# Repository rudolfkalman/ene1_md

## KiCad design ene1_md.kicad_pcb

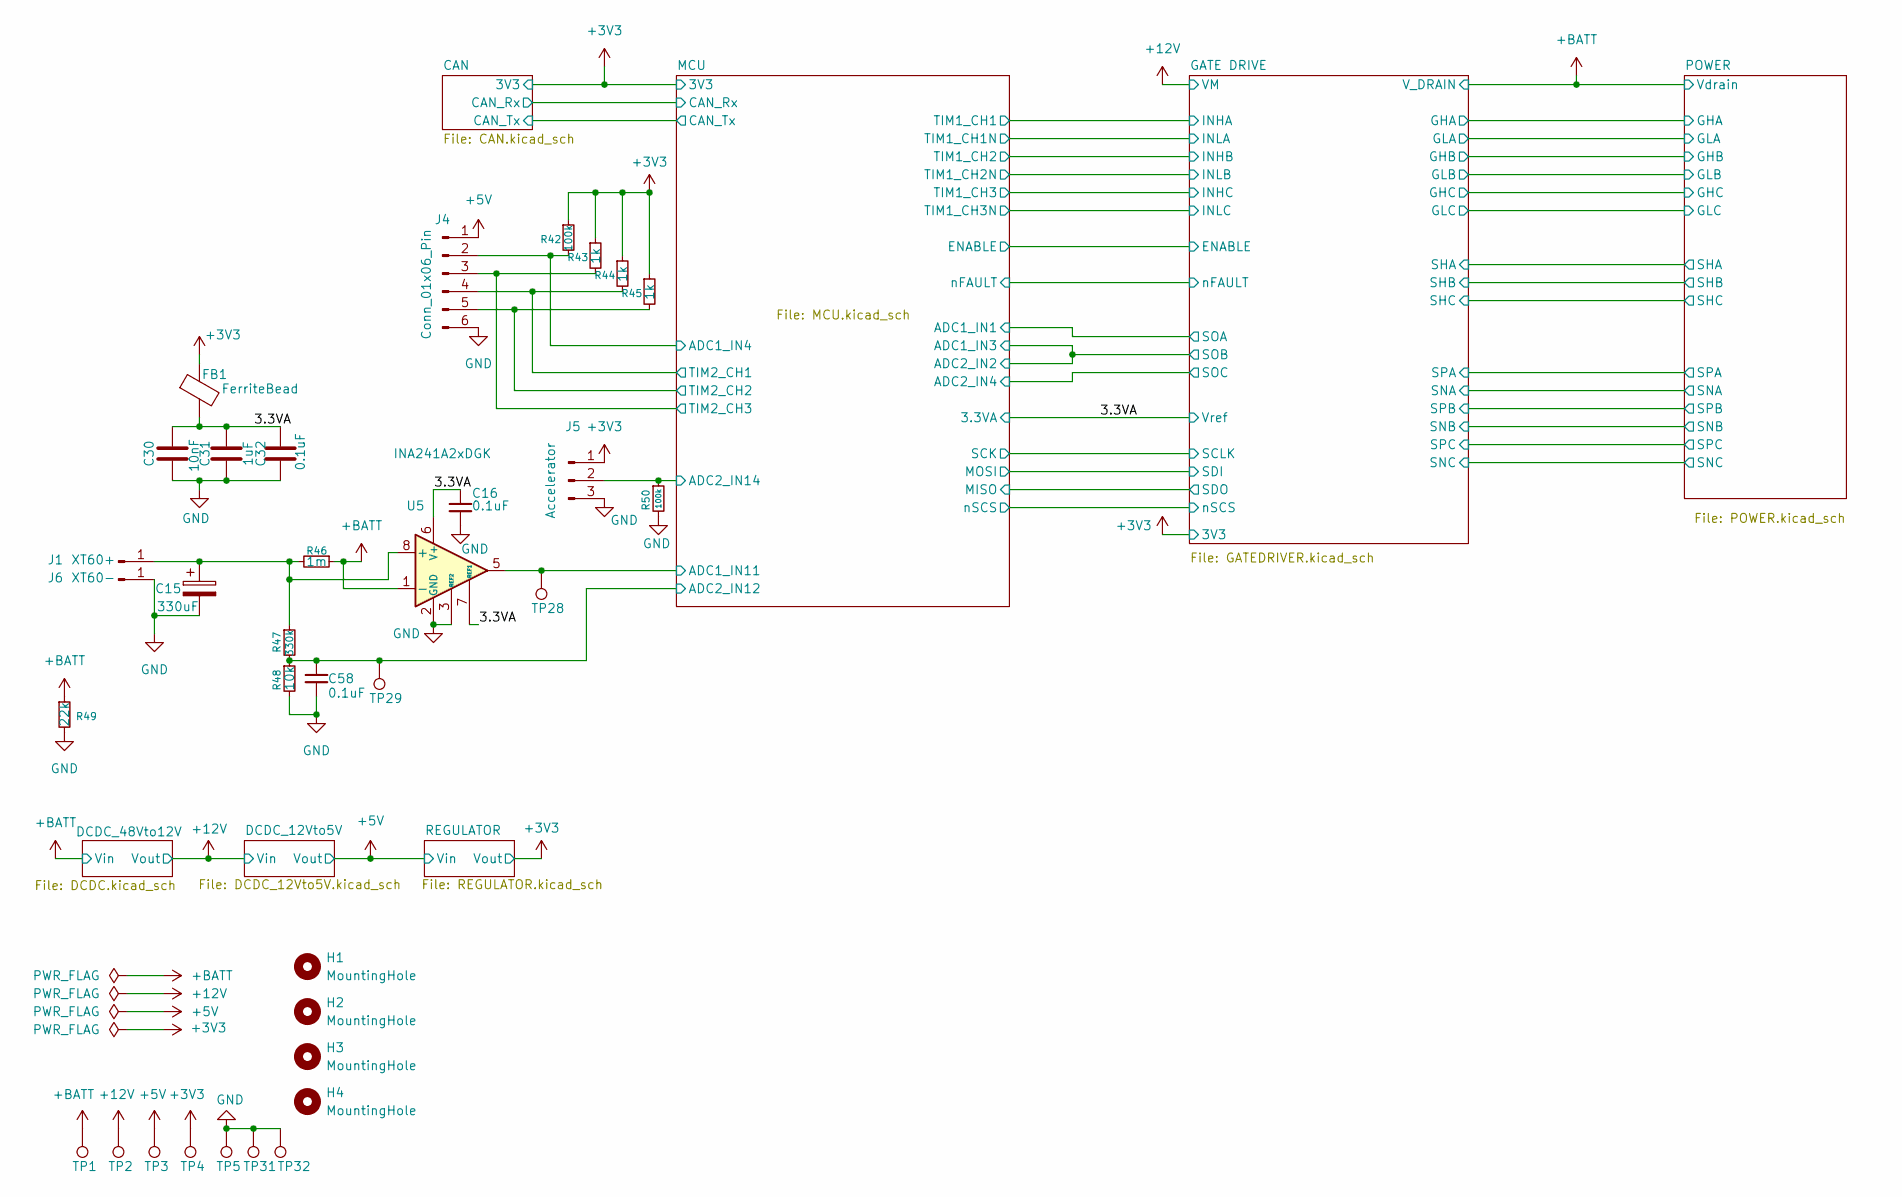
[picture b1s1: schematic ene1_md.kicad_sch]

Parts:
C15: 330uF; CP_Radial_D12.5mm_P5.00mm
C16, C32, C58: 0.1uF; C_0603_1608Metric
C30: 10nF; C_0603_1608Metric
C31: 1uF; C_0603_1608Metric
FB1: FerriteBead; L_0603_1608Metric
H1, H2, H3, H4: MountingHole; MountingHole_3.2mm_M3
J1: XT60+; SolderWirePad_1x01_SMD_5x10mm
J4: Conn_01x06_Pin; JST_XH_B6B-XH-A_1x06_P2.50mm_Vertical
J5: Accelerator; JST_XH_B6B-XH-A_1x06_P2.50mm_Vertical
J6: XT60-; SolderWirePad_1x01_SMD_5x10mm
R42: 100k; R_0805_2012Metric
R43, R44, R45: 1k; R_0603_1608Metric
R46: 1m; R_Stackpole_CSNL2512FT1L00
R47: 330k; R_0805_2012Metric
R48: 10k; R_0603_1608Metric
R49: 22k; R_Axial_DIN0207_L6.3mm_D2.5mm_P10.16mm_Horizontal
R50: 100k; R_0603_1608Metric
TP1, TP2, TP3, TP4, TP5, TP28, TP29, TP31, TP32: TestPoint; TestPoint_Pad_D1.5mm
U5: INA241A2xDGK; VSSOP-8_3x3mm_P0.65mm

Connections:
+3V3: FB1.1, J5.1, R42.1, R43.1, R44.1, R45.1, TP4.1 (1_1); also elsewhere on the board
+5V: J4.1, TP3.1 (1_1); also elsewhere on the board
+12V: TP2.1 (1_1); also elsewhere on the board
+BATT: R46.1, R49.1, TP1.1 (1_1), U5.1 (-); also elsewhere on the board
/3.3VA: C16.1, C30.2, C31.2, C32.2, FB1.2, U5.6 (V+), U5.7 (REF1); also elsewhere on the board
/MCU/ADC1_IN4: J4.2, R42.2; also elsewhere on the board
/MCU/ADC1_IN11: TP28.1 (1_1), U5.5; also elsewhere on the board
/MCU/ADC2_IN12: C58.1, R47.2, R48.1, TP29.1 (1_1); also elsewhere on the board
/MCU/ADC2_IN14: J5.2, R50.1; also elsewhere on the board
/MCU/TIM2_CH1: J4.4, R44.2; also elsewhere on the board
/MCU/TIM2_CH2: J4.5, R45.2; also elsewhere on the board
/MCU/TIM2_CH3: J4.3, R43.2; also elsewhere on the board
GND: C15.2, C16.2, C30.1, C31.1, C32.1, C58.2, J4.6, J5.3, J6.1 (Pin_1_1), R48.2, R49.2, R50.2, TP5.1 (1_1), TP31.1 (1_1), TP32.1 (1_1), U5.2 (GND), U5.3 (REF2), U5.4 (GND); also elsewhere on the board
unnamed: C15.1, J1.1 (Pin_1_1), R46.2, R47.1, U5.8 (+)

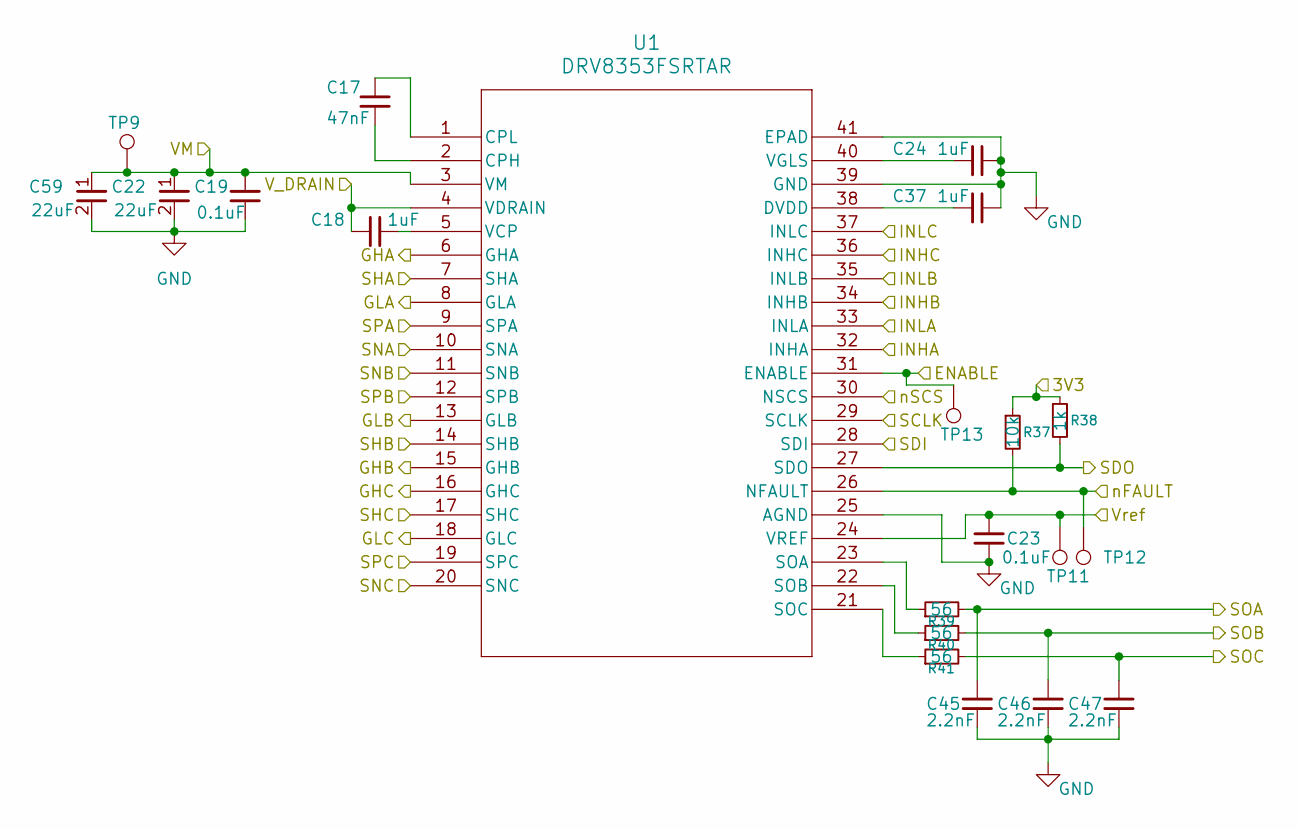
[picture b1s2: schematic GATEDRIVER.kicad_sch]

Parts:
C17: 47nF; C_0805_2012Metric
C18, C24, C37: 1uF; C_0805_2012Metric
C19, C23: 0.1uF; C_0603_1608Metric
C22, C59: 22uF; C_1206_3216Metric
C45, C46, C47: 2.2nF; C_0603_1608Metric
R37: 10k; R_0603_1608Metric
R38: 1k; R_0603_1608Metric
R39, R40, R41: 56; R_0603_1608Metric
TP9, TP11, TP12, TP13: TestPoint; TestPoint_Pad_D1.5mm
U1: DRV8353FSRTAR; WQFN40_RTA_TEX

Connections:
+3V3: R37.1, R38.1; also elsewhere on the board
+12V: C19.1, C22.1, C59.1, TP9.1 (1_1), U1.3 (VM); also elsewhere on the board
+BATT: C18.1, U1.4 (VDRAIN); also elsewhere on the board
/3.3VA: C23.1, TP11.1 (1_1), U1.24 (VREF); also elsewhere on the board
/GATE DRIVE/ENABLE: TP13.1 (1_1), U1.31 (ENABLE); also elsewhere on the board
/GATE DRIVE/GHA: U1.6 (GHA); also elsewhere on the board
/GATE DRIVE/GHB: U1.15 (GHB); also elsewhere on the board
/GATE DRIVE/GHC: U1.16 (GHC); also elsewhere on the board
/GATE DRIVE/GLA: U1.8 (GLA); also elsewhere on the board
/GATE DRIVE/GLB: U1.13 (GLB); also elsewhere on the board
/GATE DRIVE/GLC: U1.18 (GLC); also elsewhere on the board
/GATE DRIVE/INHA: U1.32 (INHA); also elsewhere on the board
/GATE DRIVE/INHB: U1.34 (INHB); also elsewhere on the board
/GATE DRIVE/INHC: U1.36 (INHC); also elsewhere on the board
/GATE DRIVE/INLA: U1.33 (INLA); also elsewhere on the board
/GATE DRIVE/INLB: U1.35 (INLB); also elsewhere on the board
/GATE DRIVE/INLC: U1.37 (INLC); also elsewhere on the board
/GATE DRIVE/SCLK: U1.29 (SCLK); also elsewhere on the board
/GATE DRIVE/SDI: U1.28 (SDI); also elsewhere on the board
/GATE DRIVE/SDO: R38.2, U1.27 (SDO); also elsewhere on the board
/GATE DRIVE/SOA: C45.1, R39.2; also elsewhere on the board
/GATE DRIVE/SOB: C46.1, R40.2; also elsewhere on the board
/GATE DRIVE/SOC: C47.1, R41.2; also elsewhere on the board
/GATE DRIVE/SPA: U1.9 (SPA); also elsewhere on the board
/GATE DRIVE/SPB: U1.12 (SPB); also elsewhere on the board
/GATE DRIVE/SPC: U1.19 (SPC); also elsewhere on the board
/GATE DRIVE/nFAULT: R37.2, TP12.1 (1_1), U1.26 (NFAULT); also elsewhere on the board
/GATE DRIVE/nSCS: U1.30 (NSCS); also elsewhere on the board
/POWER/U: U1.7 (SHA); also elsewhere on the board
/POWER/V: U1.14 (SHB); also elsewhere on the board
/POWER/W: U1.17 (SHC); also elsewhere on the board
GND: C19.2, C22.2, C23.2, C24.2, C37.2, C45.2, C46.2, C47.2, C59.2, U1.10 (SNA), U1.11 (SNB), U1.20 (SNC), U1.25 (AGND), U1.39 (GND), U1.41 (EPAD); also elsewhere on the board
unnamed: C17.2, U1.2 (CPH)
unnamed: C17.1, U1.1 (CPL)
unnamed: C37.1, U1.38 (DVDD)
unnamed: R39.1, U1.23 (SOA)
unnamed: R40.1, U1.22 (SOB)
unnamed: R41.1, U1.21 (SOC)
unnamed: C18.2, U1.5 (VCP)
unnamed: C24.1, U1.40 (VGLS)

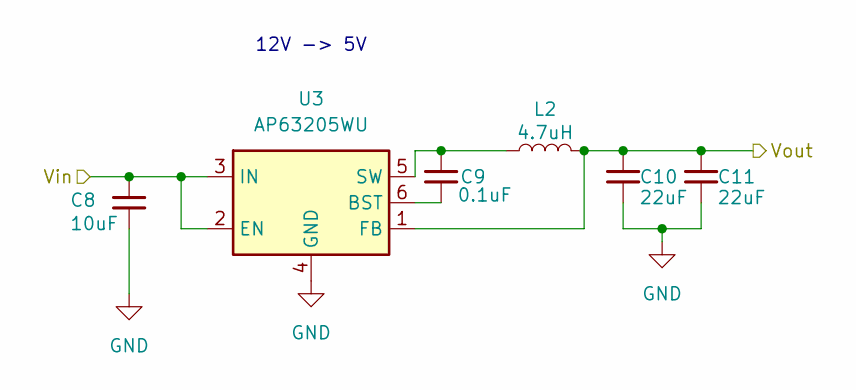
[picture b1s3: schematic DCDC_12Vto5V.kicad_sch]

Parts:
C8: 10uF; C_1206_3216Metric
C9: 0.1uF; C_0603_1608Metric
C10, C11: 22uF; C_1206_3216Metric
L2: 4.7uH; SRN5040-4R7M
U3: AP63205WU; TSOT-23-6

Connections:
+5V: C10.1, C11.1, L2.2, U3.1 (FB); also elsewhere on the board
+12V: C8.1, U3.2 (EN), U3.3 (IN); also elsewhere on the board
GND: C8.2, C10.2, C11.2, U3.4 (GND); also elsewhere on the board
unnamed: C9.2, U3.6 (BST)
unnamed: C9.1, L2.1, U3.5 (SW)

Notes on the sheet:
12V -> 5V

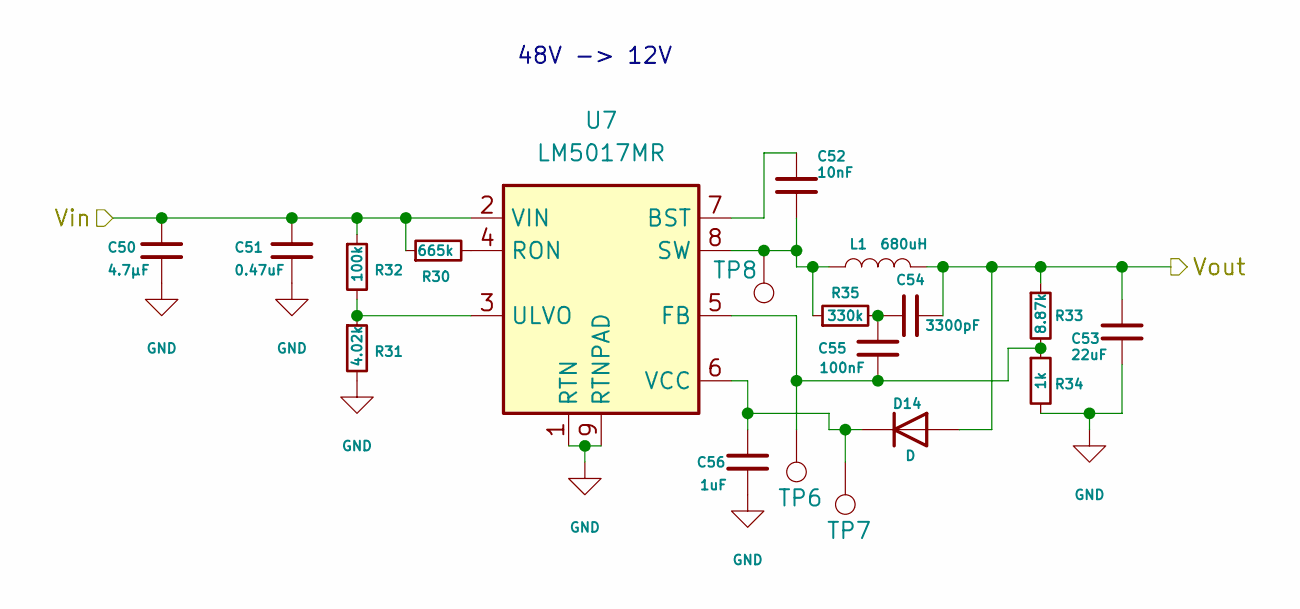
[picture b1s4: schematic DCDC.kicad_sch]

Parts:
C50: 4.7µF; C_1210_3225Metric
C51: 0.47uF; C_1206_3216Metric
C52: 10nF; C_0603_1608Metric
C53: 22uF; C_1210_3225Metric
C54: 3300pF; C_0603_1608Metric
C55: 100nF; C_0603_1608Metric
C56: 1uF; C_0603_1608Metric
D14: D; D_DO-214AC(SMA)
L1: 680uH; L_Wurth_WE-PD-1210
R30: 665k; R_0805_2012Metric
R31: 4.02k; R_0603_1608Metric
R32: 100k; R_0805_2012Metric
R33: 8.87k; R_0603_1608Metric
R34: 1k; R_0603_1608Metric
R35: 330k; R_0805_2012Metric
TP6: TestPoint; TestPoint_Pad_D1.0mm
TP7, TP8: TestPoint; TestPoint_Pad_D1.5mm
U7: LM5017MR; SOIC-8-1EP_3.9x4.9mm_P1.27mm_EP2.95x4.9mm_Mask2.71x3.4mm_Th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

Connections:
+12V: C53.1, C54.2, D14.2 (A), L1.2, R33.1; also elsewhere on the board
+BATT: C50.1, C51.1, R30.1, R32.1, U7.2 (VIN); also elsewhere on the board
GND: C50.2, C51.2, C53.2, C56.2, R31.2, R34.2, U7.1 (RTN), U7.9 (RTNPAD); also elsewhere on the board
unnamed: C54.1, C55.2, R35.2
unnamed: C56.1, D14.1 (K), TP7.1 (1_1), U7.6 (VCC)
unnamed: C52.1, U7.7 (BST)
unnamed: C55.1, R33.2, R34.1, TP6.1 (1_1), U7.5 (FB)
unnamed: R30.2, U7.4 (RON)
unnamed: C52.2, L1.1, R35.1, TP8.1 (1_1), U7.8 (SW)
unnamed: R31.1, R32.2, U7.3 (ULVO)

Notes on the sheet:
48V -> 12V

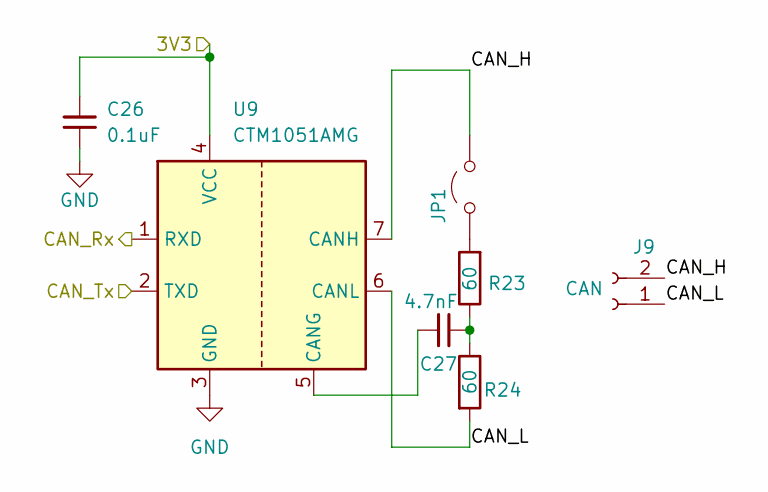
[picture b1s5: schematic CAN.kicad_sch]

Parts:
C26: 0.1uF; C_0603_1608Metric
C27: 4.7nF; C_0603_1608Metric
J9: CAN; JST_XH_B2B-XH-A_1x02_P2.50mm_Vertical
JP1: Jumper_2_Open; R_0603_1608Metric
R23, R24: 60; R_0603_1608Metric
U9: CTM1051AMG; ZLG_CTM1051AMG_12.8x10.2mm_P2.54mm

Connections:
+3V3: C26.1, U9.4 (VCC); also elsewhere on the board
/CAN/CAN_H: J9.2, JP1.2 (B), U9.7 (CANH)
/CAN/CAN_L: J9.1, R24.2, U9.6 (CANL)
/CAN/CAN_Rx: U9.1 (RXD); also elsewhere on the board
/CAN/CAN_Tx: U9.2 (TXD); also elsewhere on the board
GND: C26.2, U9.3 (GND); also elsewhere on the board
unnamed: C27.2, R23.1, R24.1
unnamed: JP1.1 (A), R23.2
unnamed: C27.1, U9.5 (CANG)

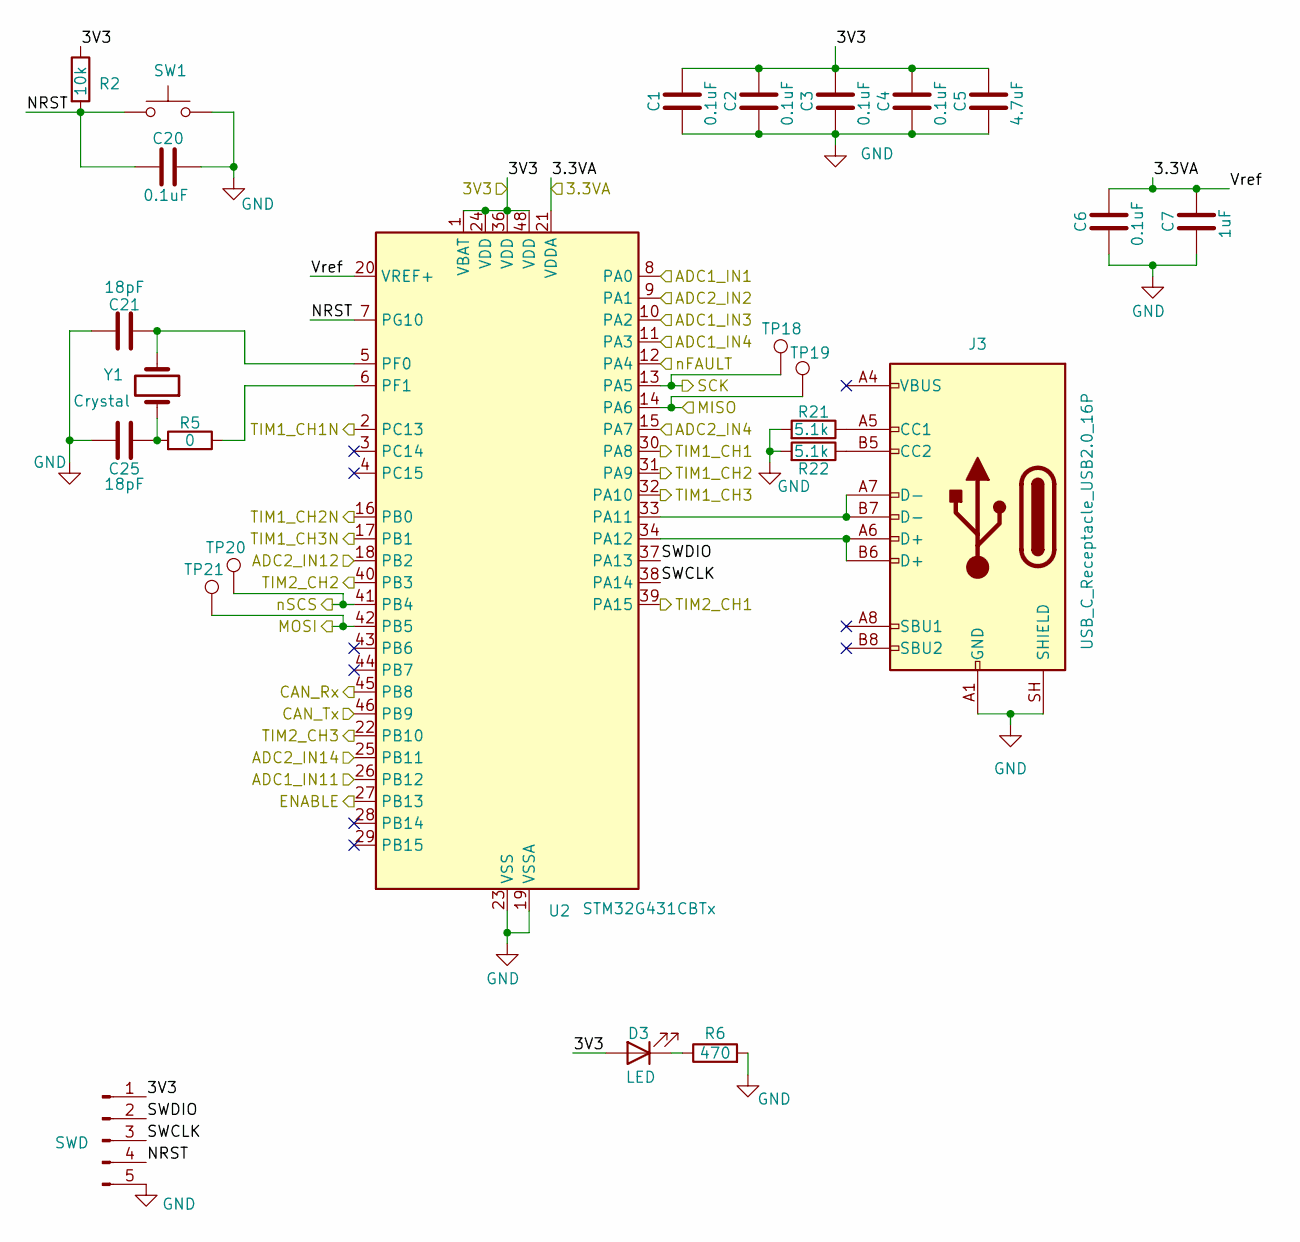
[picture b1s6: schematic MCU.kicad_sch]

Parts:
C1, C2, C3, C4, C6, C20: 0.1uF; C_0603_1608Metric
C5: 4.7uF; C_0603_1608Metric
C7: 1uF; C_0603_1608Metric
C21, C25: 18pF; C_0603_1608Metric
D3: LED; LED_0603_1608Metric
J3: USB_C_Receptacle_USB2.0_16P; USB_C_Receptacle_GCT_USB4110
R2: 10k; R_0603_1608Metric
R5: 0; R_0603_1608Metric
R6: 470; R_0603_1608Metric
R21, R22: 5.1k; R_0603_1608Metric
ST-LINK1: SWD; PinHeader_1x05_P2.54mm_Vertical
SW1: SW_Push; SW_Tactile_SPST_NO_Straight_CK_PTS636Sx25SMTRLFS
TP18, TP19, TP20, TP21: TestPoint; TestPoint_Pad_D1.5mm
U2: STM32G431CBTx; LQFP-48_7x7mm_P0.5mm
Y1: Crystal; Crystal_SMD_3225-4Pin_3.2x2.5mm

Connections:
+3V3: C1.2, C2.2, C3.2, C4.2, C5.2, D3.2 (A), R2.1, ST-LINK1.1, U2.1 (VBAT), U2.24 (VDD), U2.36 (VDD), U2.48 (VDD); also elsewhere on the board
/3.3VA: C6.2, C7.2, U2.20 (VREF+), U2.21 (VDDA); also elsewhere on the board
/CAN/CAN_Rx: U2.45 (PB8); also elsewhere on the board
/CAN/CAN_Tx: U2.46 (PB9); also elsewhere on the board
/GATE DRIVE/ENABLE: U2.27 (PB13); also elsewhere on the board
/GATE DRIVE/INHA: U2.30 (PA8); also elsewhere on the board
/GATE DRIVE/INHB: U2.31 (PA9); also elsewhere on the board
/GATE DRIVE/INHC: U2.32 (PA10); also elsewhere on the board
/GATE DRIVE/INLA: U2.2 (PC13); also elsewhere on the board
/GATE DRIVE/INLB: U2.16 (PB0); also elsewhere on the board
/GATE DRIVE/INLC: U2.17 (PB1); also elsewhere on the board
/GATE DRIVE/SCLK: TP18.1 (1_1), U2.13 (PA5); also elsewhere on the board
/GATE DRIVE/SDI: TP21.1 (1_1), U2.42 (PB5); also elsewhere on the board
/GATE DRIVE/SDO: TP19.1 (1_1), U2.14 (PA6); also elsewhere on the board
/GATE DRIVE/SOA: U2.8 (PA0); also elsewhere on the board
/GATE DRIVE/SOB: U2.9 (PA1), U2.10 (PA2); also elsewhere on the board
/GATE DRIVE/SOC: U2.15 (PA7); also elsewhere on the board
/GATE DRIVE/nFAULT: U2.12 (PA4); also elsewhere on the board
/GATE DRIVE/nSCS: TP20.1 (1_1), U2.41 (PB4); also elsewhere on the board
/MCU/ADC1_IN4: U2.11 (PA3); also elsewhere on the board
/MCU/ADC1_IN11: U2.26 (PB12); also elsewhere on the board
/MCU/ADC2_IN12: U2.18 (PB2); also elsewhere on the board
/MCU/ADC2_IN14: U2.25 (PB11); also elsewhere on the board
/MCU/NRST: C20.1, R2.2, ST-LINK1.4, SW1.1, U2.7 (PG10)
/MCU/SWCLK: ST-LINK1.3, U2.38 (PA14)
/MCU/SWDIO: ST-LINK1.2, U2.37 (PA13)
/MCU/TIM2_CH1: U2.39 (PA15); also elsewhere on the board
/MCU/TIM2_CH2: U2.40 (PB3); also elsewhere on the board
/MCU/TIM2_CH3: U2.22 (PB10); also elsewhere on the board
GND: C1.1, C2.1, C3.1, C4.1, C5.1, C6.1, C7.1, C20.2, C21.2, C25.1, J3.A1 (GND), J3.A12 (GND), J3.B1 (GND), J3.B12 (GND), J3.SH (SHIELD), R6.2, R21.2, R22.2, ST-LINK1.5, SW1.2, U2.19 (VSSA), U2.23 (VSS), U2.35 (VSS), U2.47 (VSS); also elsewhere on the board
unnamed: C25.2, R5.2, Y1.1
unnamed: D3.1 (K), R6.1
unnamed: J3.A5 (CC1), R21.1
unnamed: J3.B5 (CC2), R22.1
unnamed: J3.A7 (D-), J3.B7 (D-), U2.33 (PA11)
unnamed: J3.A6 (D+), J3.B6 (D+), U2.34 (PA12)
unnamed: C21.1, U2.5 (PF0), Y1.2
unnamed: R5.1, U2.6 (PF1)

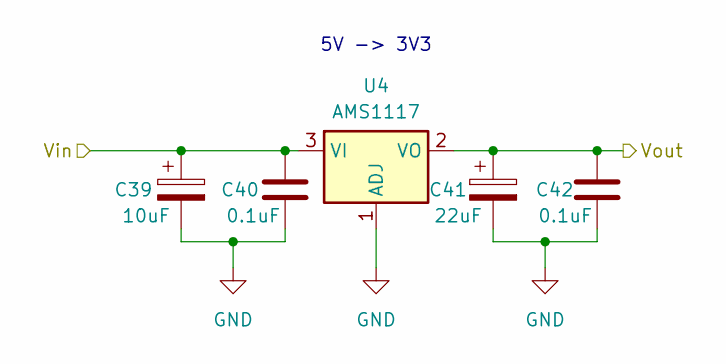
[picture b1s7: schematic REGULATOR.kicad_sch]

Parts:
C39: 10uF; C_CASE-A-3216-18(mm)
C40, C42: 0.1uF; C_0603_1608Metric
C41: 22uF; C_CASE-A-3216-18(mm)
U4: AMS1117; SOT-223-3_TabPin2

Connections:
+3V3: C41.1, C42.1, U4.2 (VO); also elsewhere on the board
+5V: C39.1, C40.1, U4.3 (VI); also elsewhere on the board
GND: C39.2, C40.2, C41.2, C42.2, U4.1 (ADJ); also elsewhere on the board

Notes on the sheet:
5V -> 3V3

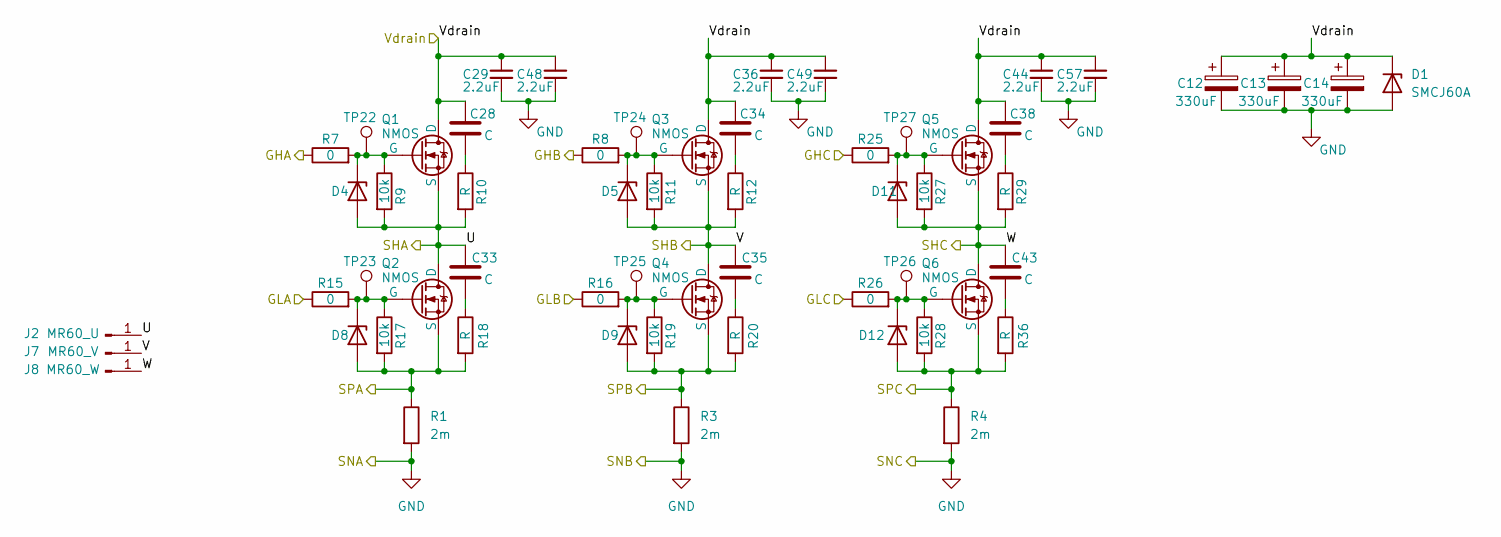
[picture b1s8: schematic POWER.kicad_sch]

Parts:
C12, C13, C14: 330uF; CP_Radial_D12.5mm_P5.00mm
C28, C33, C34, C35, C38, C43: C; C_0805_2012Metric
C29, C36, C44, C48, C49, C57: 2.2uF; C_1210_3225Metric
D1: SMCJ60A; D_SMC
D4, D5, D8, D9, D11, D12: D_Zener; D_SOD-123
J2: MR60_U; SolderWirePad_1x01_SMD_5x10mm
J7: MR60_V; SolderWirePad_1x01_SMD_5x10mm
J8: MR60_W; SolderWirePad_1x01_SMD_5x10mm
Q1, Q2, Q3, Q4, Q5, Q6: NMOS; TPH2R70AR5_SOP-Advance-N
R1, R3, R4: 2m; R_Bourns_CRE2512-FZ-R002E-3
R7, R8, R15, R16, R25, R26: 0; R_0603_1608Metric
R9, R11, R17, R19, R27, R28: 10k; R_0603_1608Metric
R10, R12, R18, R20, R29, R36: R; R_0805_2012Metric
TP22, TP23, TP24, TP25, TP26, TP27: TestPoint; TestPoint_Pad_D1.5mm

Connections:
+BATT: C12.1, C13.1, C14.1, C28.1, C29.1, C34.1, C36.1, C38.1, C44.1, C48.1, C49.1, C57.1, D1.1 (K), Q1.1 (D), Q3.1 (D), Q5.1 (D); also elsewhere on the board
/GATE DRIVE/GHA: R7.1; also elsewhere on the board
/GATE DRIVE/GHB: R8.1; also elsewhere on the board
/GATE DRIVE/GHC: R25.1; also elsewhere on the board
/GATE DRIVE/GLA: R15.1; also elsewhere on the board
/GATE DRIVE/GLB: R16.1; also elsewhere on the board
/GATE DRIVE/GLC: R26.1; also elsewhere on the board
/GATE DRIVE/SPA: D8.2 (A), Q2.3 (S), R1.1, R17.2, R18.2; also elsewhere on the board
/GATE DRIVE/SPB: D9.2 (A), Q4.3 (S), R3.1, R19.2, R20.2; also elsewhere on the board
/GATE DRIVE/SPC: D12.2 (A), Q6.3 (S), R4.1, R28.2, R36.2; also elsewhere on the board
/POWER/U: C33.1, D4.2 (A), J2.1 (Pin_1_1), Q1.3 (S), Q2.1 (D), R9.2, R10.2; also elsewhere on the board
/POWER/V: C35.1, D5.2 (A), J7.1 (Pin_1_1), Q3.3 (S), Q4.1 (D), R11.2, R12.2; also elsewhere on the board
/POWER/W: C43.1, D11.2 (A), J8.1 (Pin_1_1), Q5.3 (S), Q6.1 (D), R27.2, R29.2; also elsewhere on the board
GND: C12.2, C13.2, C14.2, C29.2, C36.2, C44.2, C48.2, C49.2, C57.2, D1.2 (A), R1.2, R3.2, R4.2; also elsewhere on the board
unnamed: C28.2, R10.1
unnamed: C33.2, R18.1
unnamed: C34.2, R12.1
unnamed: C35.2, R20.1
unnamed: C38.2, R29.1
unnamed: C43.2, R36.1
unnamed: D4.1 (K), Q1.2 (G), R7.2, R9.1, TP22.1 (1_1)
unnamed: D5.1 (K), Q3.2 (G), R8.2, R11.1, TP24.1 (1_1)
unnamed: D8.1 (K), Q2.2 (G), R15.2, R17.1, TP23.1 (1_1)
unnamed: D9.1 (K), Q4.2 (G), R16.2, R19.1, TP25.1 (1_1)
unnamed: D11.1 (K), Q5.2 (G), R25.2, R27.1, TP27.1 (1_1)
unnamed: D12.1 (K), Q6.2 (G), R26.2, R28.1, TP26.1 (1_1)

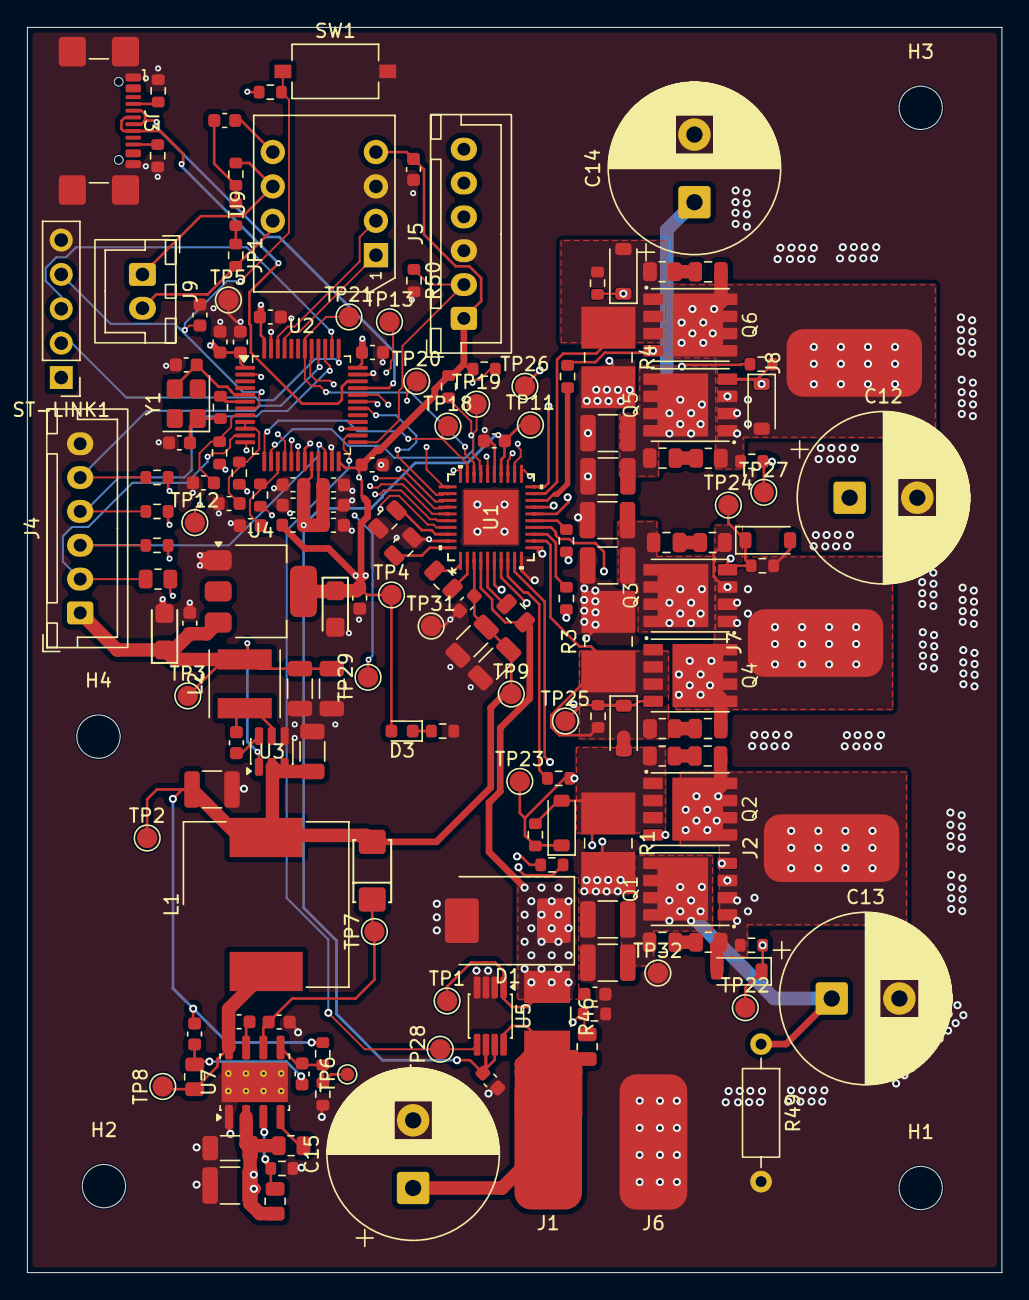
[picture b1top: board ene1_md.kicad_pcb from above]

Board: 4 copper layers, 72.0 x 92.0 mm, 175 parts (0 on the bottom side), 88 nets.

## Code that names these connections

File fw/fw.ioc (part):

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Mcu.Name=STM32G431C(6-8-B)Tx
Mcu.Package=LQFP48
Mcu.UserName=STM32G431CBTx
PA0.Mode=IN1-Single-Ended
PA0.Signal=ADC1_IN1
PA1.Mode=IN2-Single-Ended
PA1.Signal=ADC2_IN2
PA10.Signal=S_TIM1_CH3
PA11.Mode=Device
PA11.Signal=USB_DM
PA12.Mode=Device
PA12.Signal=USB_DP
PA13.Mode=Serial_Wire
PA13.Signal=SYS_JTMS-SWDIO
PA14.Mode=Serial_Wire
PA14.Signal=SYS_JTCK-SWCLK
PA15.Signal=S_TIM2_CH1
PA2.Mode=IN3-Single-Ended
PA2.Signal=ADC1_IN3
PA3.Mode=IN4-Single-Ended
PA3.Signal=ADC1_IN4
PA4.Signal=GPIO_Input
PA5.Mode=Full_Duplex_Master
PA5.Signal=SPI1_SCK
PA6.Mode=Full_Duplex_Master
PA6.Signal=SPI1_MISO
PA7.Mode=IN4-Single-Ended
PA7.Signal=ADC2_IN4
PA8.Signal=S_TIM1_CH1
PA9.Signal=S_TIM1_CH2
PB0.Mode=Output Compare2 CH2 CH2N
PB0.Signal=TIM1_CH2N
PB1.Mode=Output Compare3 CH3 CH3N
PB1.Signal=TIM1_CH3N
PB10.Signal=S_TIM2_CH3
PB11.Mode=IN14-Single-Ended
PB11.Signal=ADC2_IN14
PB12.Mode=IN11-Single-Ended
PB12.Signal=ADC1_IN11
PB13.Signal=GPIO_Output
PB14.Signal=GPIO_Output
PB15.Signal=GPIO_Output
PB2.Mode=IN12-Single-Ended
PB2.Signal=ADC2_IN12
PB3.Signal=S_TIM2_CH2
PB4.Signal=GPIO_Output
PB5.Mode=Full_Duplex_Master
PB5.Signal=SPI1_MOSI
PB8-BOOT0.Mode=FDCAN_Activate
PB8-BOOT0.Signal=FDCAN1_RX
PB9.Mode=FDCAN_Activate
PB9.Signal=FDCAN1_TX
PC13.Mode=Output Compare1 CH1 CH1N
PC13.Signal=TIM1_CH1N
PF0-OSC_IN.Mode=HSE-External-Oscillator
PF0-OSC_IN.Signal=RCC_OSC_IN
PF1-OSC_OUT.Mode=HSE-External-Oscillator
PF1-OSC_OUT.Signal=RCC_OSC_OUT
RCC.HSE_VALUE=8000000
RCC.SYSCLKFreq_VALUE=16000000
board=custom
